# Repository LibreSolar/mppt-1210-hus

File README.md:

# 10A MPPT Charge Controller with USB

 Evaluation phase

User manual: [HTML](https://libre.solar/mppt-1210-hus/) / [PDF](https://libre.solar/mppt-1210-hus/manual.pdf)

Schematic: [PDF file](build/mppt-1210-hus_schematic.pdf)

Bill of Materials: [CSV file](build/mppt-1210-hus_bom.csv) or [interactive HTML BOM](https://libre.solar/mppt-1210-hus/mppt-1210-hus_ibom.html)

Firmware repository: [LibreSolar/charge-controller-firmware](https://github.com/LibreSolar/charge-controller-firmware)

## Features:

- 12V battery voltage
- 40V max. solar input (36 to 48-cell panels, ideally so-called 12V panels with 36 cells)
- 10A max. charge current
- 10A max. load output current
- Low-power 32bit ARM MCU (STM32L072)
- Expandable via Olimex Universal Extension Connector (UEXT) featuring
   I2C, Serial and SPI interface (e.g. used for display, WIFI communication, etc.)
- USB charging
- High-side load switching

## Built-in protection:

- Overvoltage
- Undervoltage
- Overcurrent
- PV short circuit
- PV reverse polarity
- Battery reverse polarity (destructive, fuse is blown)

## Manual

The manual is auto-generated from the markdown files in the `manual` subfolder. See [here](https://github.com/LibreSolar/md-manual-template) for further information regarding the automated deployment.

You can contribute to the manual by cloning the repository to your private GitHub workspace and sending pull-requests with upates you made.

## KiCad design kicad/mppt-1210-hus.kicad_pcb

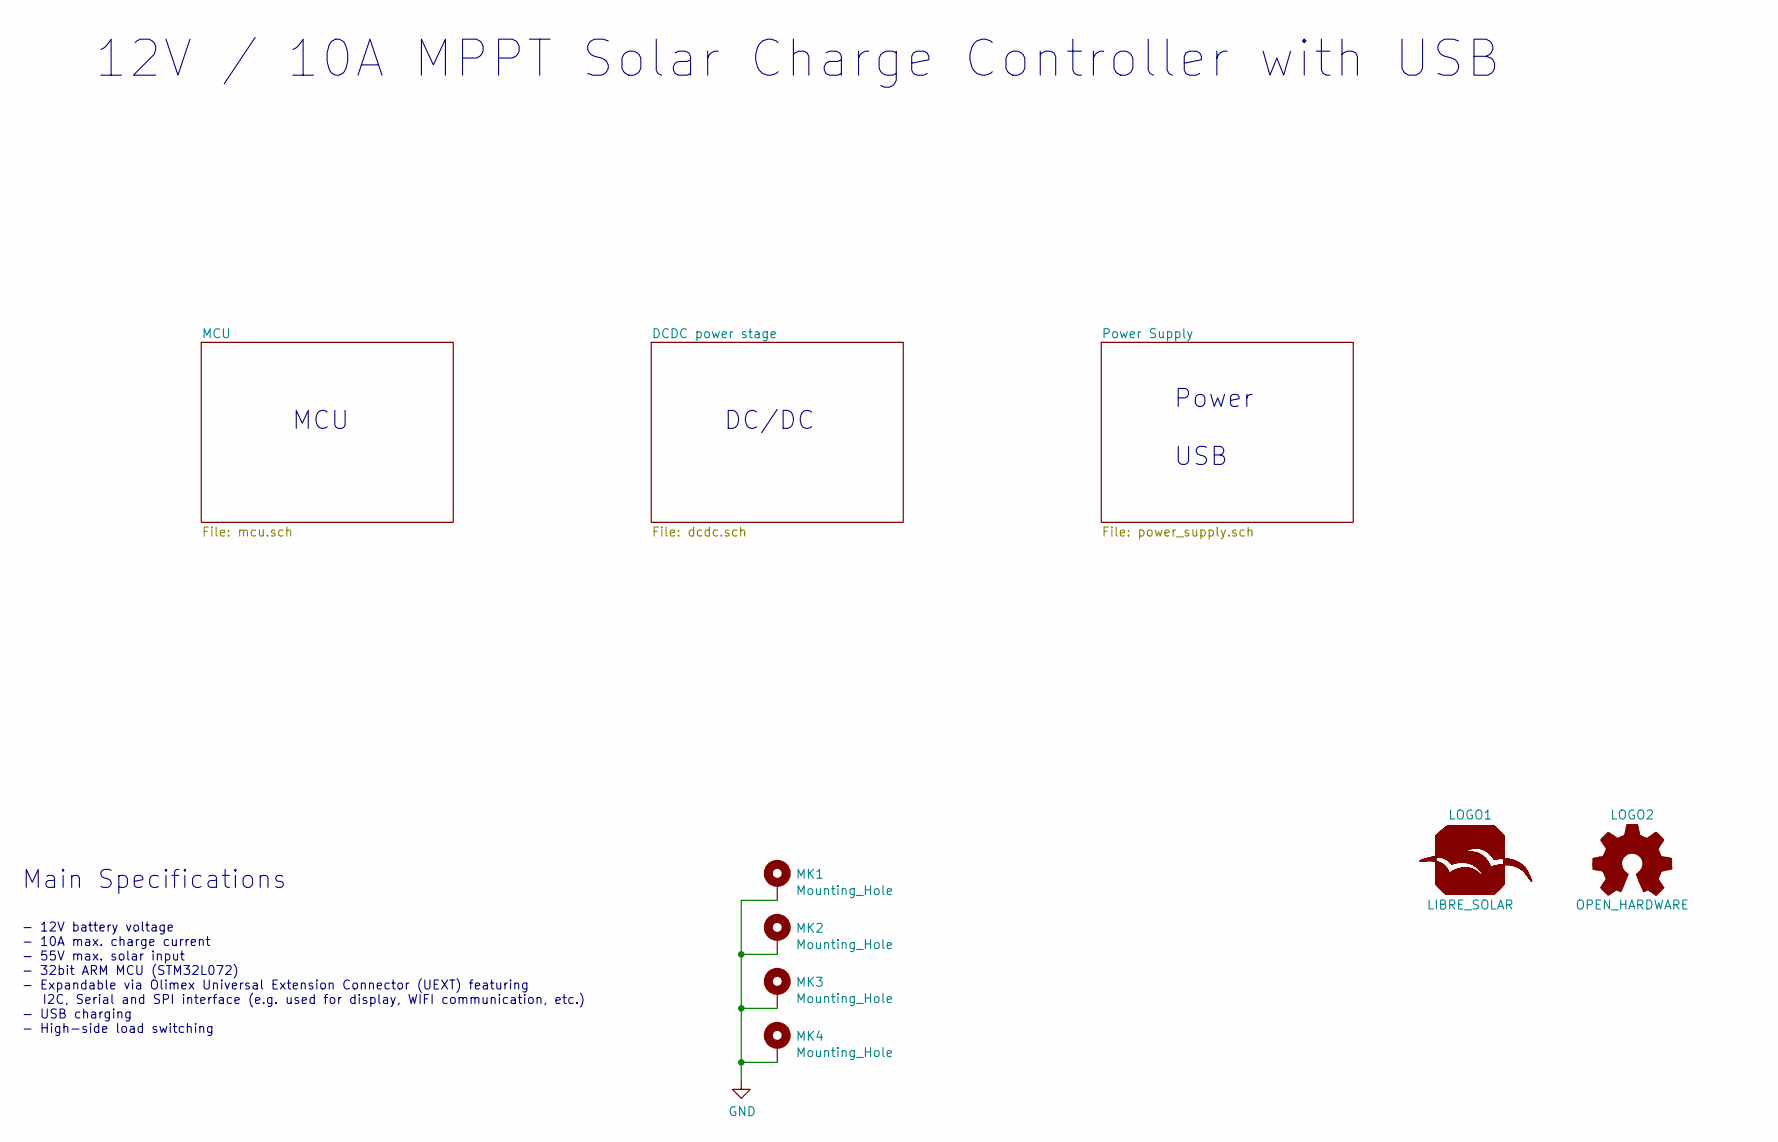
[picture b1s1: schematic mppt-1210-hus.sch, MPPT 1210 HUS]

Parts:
LOGO1: LIBRE_SOLAR; LIBRESOLAR_LOGO
LOGO2: OPEN_HARDWARE; OSHW-Logo_5.7x6mm_SilkScreen
MK1, MK2, MK3, MK4: Mounting_Hole; MountingHole_3.2mm_M3_Pad

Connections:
GND: MK1.1, MK2.1, MK3.1, MK4.1; also elsewhere on the board

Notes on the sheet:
12V / 10A MPPT Solar Charge Controller with USB
Main Specifications
- 12V battery voltage - 10A max. charge current - 55V max. solar input - 32bit ARM MCU (STM32L072) - Expandable via Olimex Universal Extension Connector (UEXT) featuring I2C, Serial and SPI interface (e.g. used for display, WIFI communication, etc.) - USB charging - High-side load switching
DC/DC
MCU
Power USB

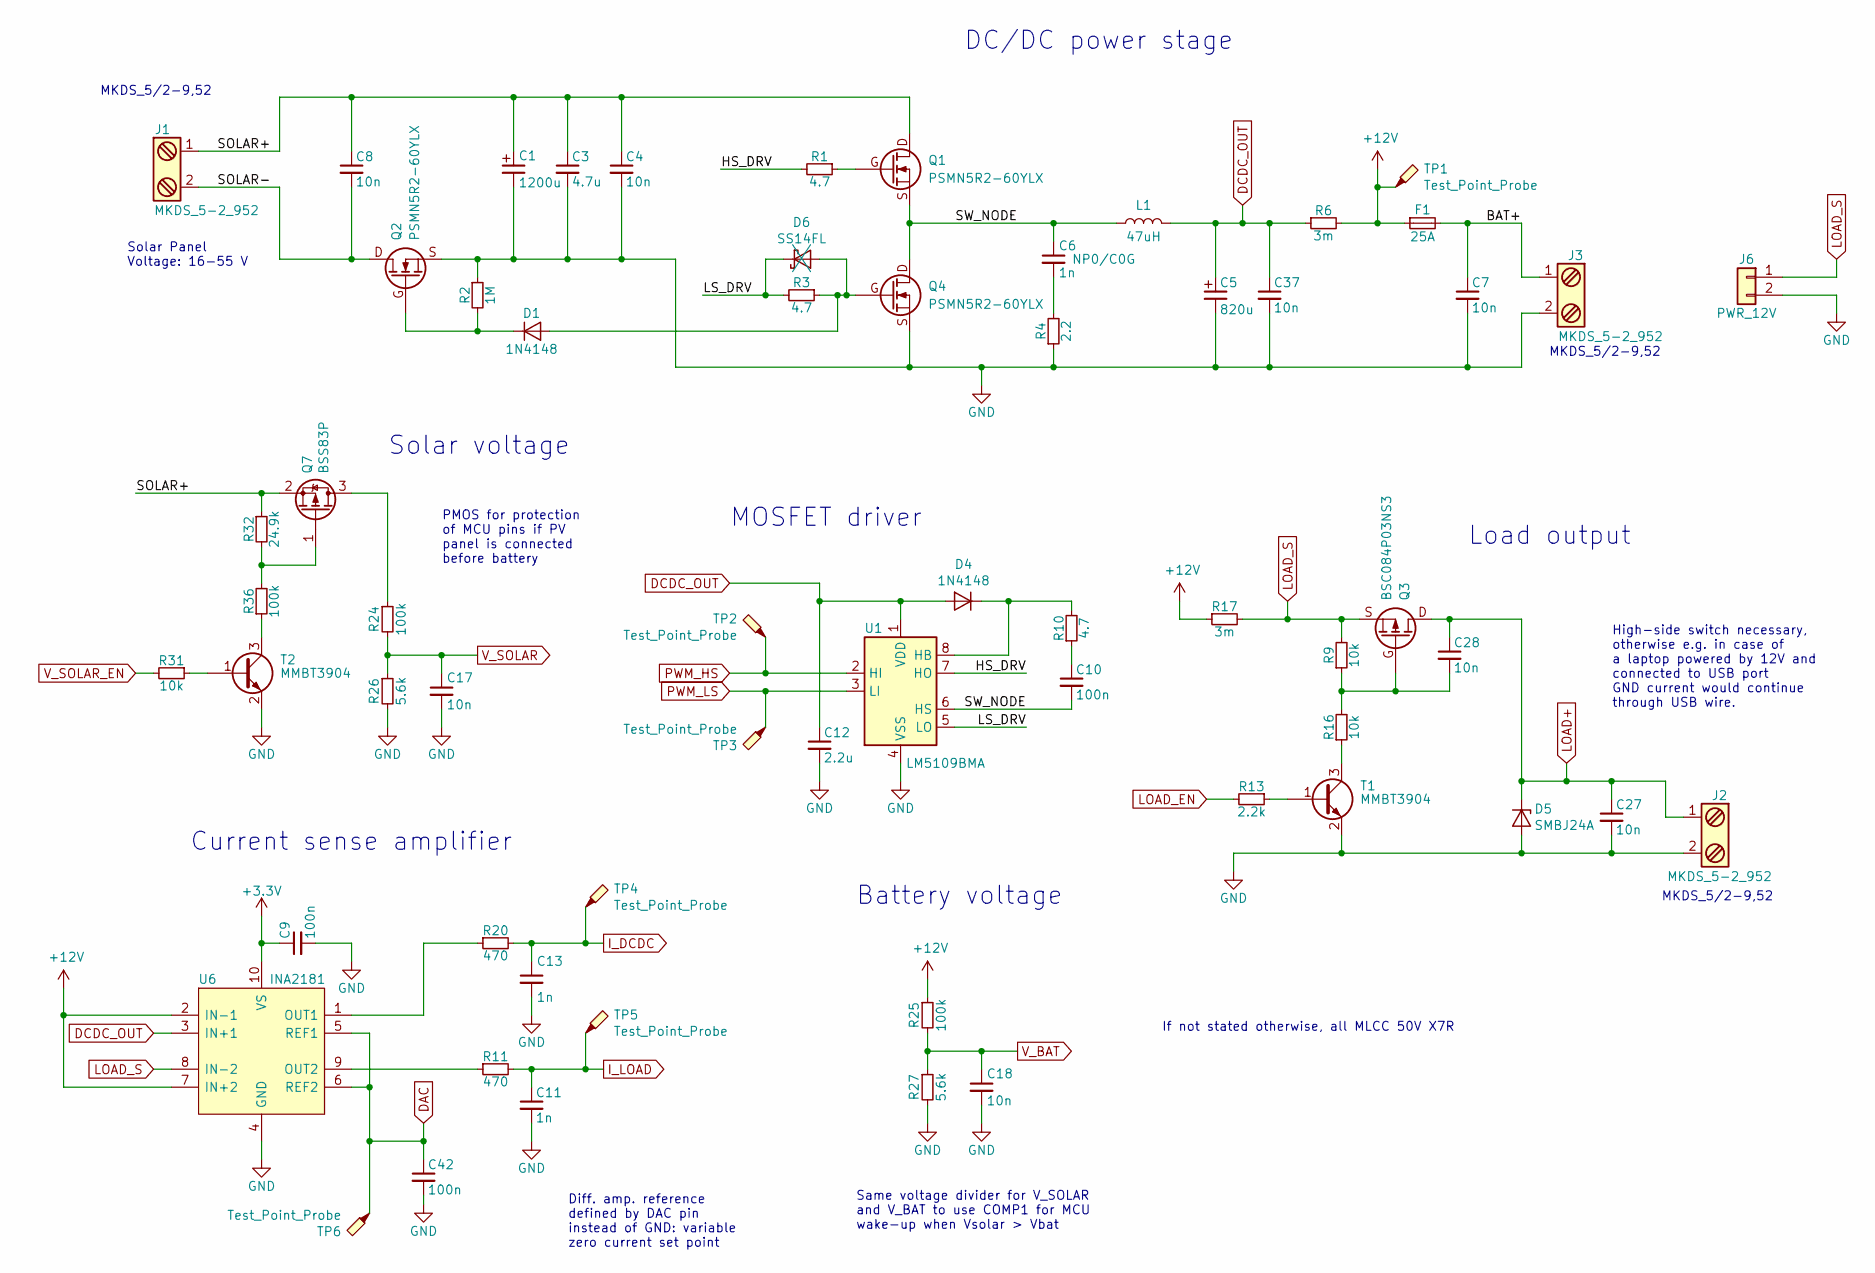
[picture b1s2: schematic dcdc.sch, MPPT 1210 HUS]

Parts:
C1: 1200u; CP_Radial_L31.5mm_D16.0mm_P7.50mm_horizontal; PartNumber EKYB630ELL122MLN3S
C3: 4.7u; C_1210_3225; PartNumber GRJ32DC72A475KE11L
C4, C7, C8, C17, C18, C27, C28, C37: 10n; C_0603_1608; PartNumber GCM188R72A103KA37D
C5: 820u; CP_Radial_D10.0mm_P5.00mm; PartNumber EEU-FR1E821
C6, C11, C13: 1n; C_0603_1608; PartNumber GRM1885C2A102JA01D
C9, C10, C42: 100n; C_0603_1608; PartNumber CC0603KRX7R9BB104
C12: 2.2u; C_0603_1608; PartNumber GRM188R61E225KA12D
D1, D4: 1N4148; D_SOD-123; PartNumber 1N4148W-7-F
D5: SMBJ24A; D_SMB; PartNumber SMBJ24A
D6: SS14FL; D_SOD-123; PartNumber SS14FL
F1: 25A; KEYSTONE-FUSE-3557-2; PartNumber 3557-2
J1, J2, J3: MKDS_5-2_952; Phoenix_Contact_MKDS_5-2-952; PartNumber 1714971
J6: PWR_12V; JST_XH_B02B-XH-A_1x02_P2.50mm_Vertical; PartNumber B2B-XH-A (LF)(SN)
L1: 47uH; L-FERYSTER-DTMSS-27_47uH; PartNumber DTMSS-27/0,047/15-HX
Q1, Q2, Q4: PSMN5R2-60YLX; 5X6_MOSFET; PartNumber PSMN5R2-60YLX
Q3: BSC084P03NS3; 5X6_MOSFET; PartNumber BSC084P03NS3GATMA1
Q7: BSS83P; SOT-23; PartNumber BSS83P H6327
R1, R3, R10: 4.7; R_0805_2012; PartNumber RC0805FR-074R7L
R2: 1M; R_0603_1608; PartNumber RC0603FR-071ML
R4: 2.2; R_1206_3216; PartNumber RC1206FR-072R2L
R6, R17: 3m; R_Bourns_CRE2512; PartNumber CRE2512-FZ-R003E-3
R9, R16, R31: 10k; R_0603_1608; PartNumber RC0603FR-0710KL
R11, R20: 470; R_0603_1608; PartNumber RC0603FR-07470RL
R13: 2.2k; R_0603_1608; PartNumber RC0603FR-072K2L
R24, R25, R36: 100k; R_0603_1608; PartNumber RC0603FR-07100KL
R26, R27: 5.6k; R_0603_1608; PartNumber RC0603FR-075K6L
R32: 24.9k; R_0603_1608; PartNumber RC0603FR-0724K9L
T1, T2: MMBT3904; SOT-23; PartNumber MMBT3904-7-F
TP1, TP2, TP3, TP4, TP5, TP6: Test_Point_Probe; TestPoint_Pad_D1.0mm
U1: LM5109BMA; SOIC-8_3.9x4.9mm_Pitch1.27mm; PartNumber LM5109BMAX/NOPB
U6: INA2181; VSSOP-10_3.0x3.0mm_P0.5mm; PartNumber INA2181A2IDGS

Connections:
+3V3: C9.1, U6.10 (VS); also elsewhere on the board
+12V: F1.1, R6.2, R17.1, R25.1, TP1.1, U6.2 (IN-1), U6.7 (IN+2)
/DCDC power stage/BAT+: C7.1, F1.2, J3.1
/DCDC power stage/HS_DRV: R1.2, U1.7 (HO)
/DCDC power stage/LS_DRV: D6.1 (K), R3.2, U1.5 (LO)
/DCDC power stage/SOLAR+: C1.1, C3.1, C4.1, C8.1, J1.1, Q1.D, Q7.2 (S), R32.1
/DCDC power stage/SOLAR-: C8.2, J1.2, Q2.D
/DCDC power stage/SW_NODE: C6.1, C10.2, L1.1, Q1.S, Q4.D, U1.6 (HS)
DAC: C42.1, TP6.1, U6.5 (REF1), U6.6 (REF2); also elsewhere on the board
DCDC_OUT: C5.1, C12.1, C37.1, D4.2 (A), L1.2, R6.1, U1.1 (VDD), U6.3 (IN+1); also elsewhere on the board
GND: C1.2, C3.2, C4.2, C5.2, C7.2, C9.2, C11.2, C12.2, C13.2, C17.2, C18.2, C27.2, C37.2, C42.2, D5.2 (A), J2.2, J3.2, J6.2, Q2.S, Q4.S, R2.1, R4.1, R26.2, R27.2, T1.2 (E), T2.2 (E), U1.4 (VSS), U6.4 (GND); also elsewhere on the board
I_DCDC: C13.1, R20.2, TP4.1; also elsewhere on the board
I_LOAD: C11.1, R11.2, TP5.1; also elsewhere on the board
LOAD+: C27.1, C28.1, D5.1 (K), J2.1, Q3.D
LOAD_EN: R13.2; also elsewhere on the board
LOAD_S: J6.1, Q3.S, R9.2, R17.2, U6.8 (IN-2); also elsewhere on the board
unnamed: C6.2, R4.2
unnamed: C10.1, R10.1
unnamed: C28.2, Q3.G, R9.1, R16.2
unnamed: D1.1 (K), Q2.G, R2.2
unnamed: D1.2 (A), D6.2 (A), Q4.G, R3.1
unnamed: D4.1 (K), R10.2, U1.8 (HB)
unnamed: Q1.G, R1.1
unnamed: Q7.1 (G), R32.2, R36.2
unnamed: Q7.3 (D), R24.1
unnamed: R11.1, U6.9 (OUT2)
unnamed: R13.1, T1.1 (B)
unnamed: R16.1, T1.3 (C)
unnamed: R20.1, U6.1 (OUT1)
unnamed: R31.1, T2.1 (B)
unnamed: R36.1, T2.3 (C)
PWM_HS: TP2.1, U1.2 (HI); also elsewhere on the board
PWM_LS: TP3.1, U1.3 (LI); also elsewhere on the board
V_BAT: C18.1, R25.2, R27.1; also elsewhere on the board
V_SOLAR: C17.1, R24.2, R26.1; also elsewhere on the board
V_SOLAR_EN: R31.2; also elsewhere on the board

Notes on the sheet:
Solar Panel Voltage: 16-55 V
DC/DC power stage
Load output
MOSFET driver
If not stated otherwise, all MLCC 50V X7R
MKDS_5/2-9,52
Current sense amplifier
Solar voltage
Diff. amp. reference defined by DAC pin instead of GND: variable zero current set point
Same voltage divider for V_SOLAR and V_BAT to use COMP1 for MCU wake-up when Vsolar > Vbat
High-side switch necessary, otherwise e.g. in case of a laptop powered by 12V and connected to USB port GND current would continue through USB wire.
Battery voltage
PMOS for protection of MCU pins if PV panel is connected before battery

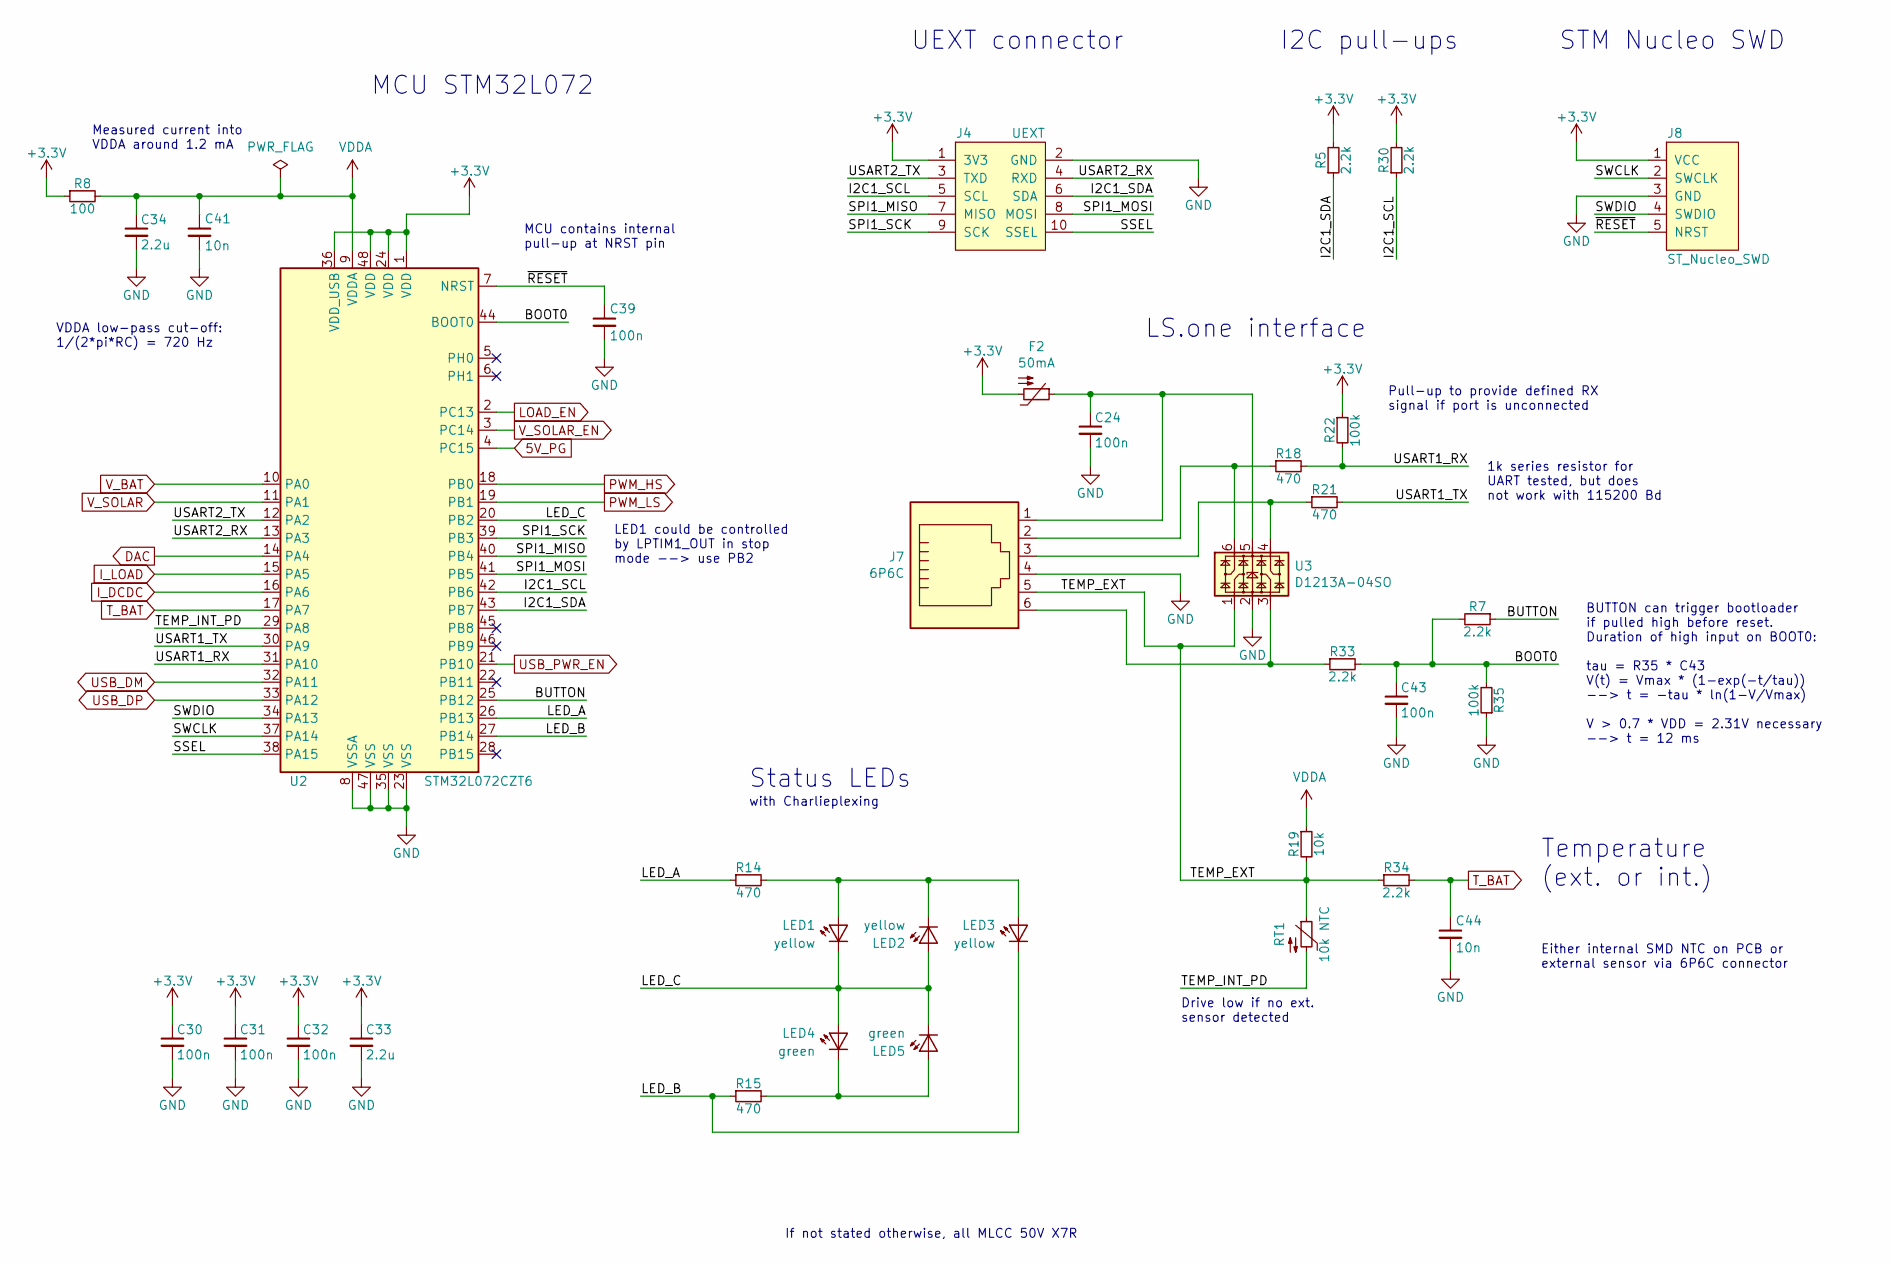
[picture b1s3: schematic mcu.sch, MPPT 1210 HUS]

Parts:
C24, C30, C31, C32, C39, C43: 100n; C_0603_1608; PartNumber CC0603KRX7R9BB104
C33, C34: 2.2u; C_0603_1608; PartNumber GRM188R61E225KA12D
C41, C44: 10n; C_0603_1608; PartNumber GCM188R72A103KA37D
F2: 50mA; R_1206_3216; PartNumber 0ZCJ0005FF2E
J4: UEXT; Box_Header_2x05x2.54mm_Straight; PartNumber 302-S101
J7: 6P6C; RJ25_6P6C_TabUp; PartNumber 615006138421
J8: ST_Nucleo_SWD; PinHeader_1x05_P2.54mm_Vertical; PartNumber M20-9990546
LED1, LED3: yellow; LED_0603_D3.0mm; PartNumber LTST-C191KSKT
LED2, LED5: green; LED_0603_D3.0mm; PartNumber LTST-C190KGKT
R5, R7, R30, R33, R34: 2.2k; R_0603_1608; PartNumber RC0603FR-072K2L
R8: 100; R_0603_1608; PartNumber RC0603FR-07100RL
R14, R15, R18, R21: 470; R_0603_1608; PartNumber RC0603FR-07470RL
R19: 10k; R_0603_1608; PartNumber RC0603FR-0710KL
R22, R35: 100k; R_0603_1608; PartNumber RC0603FR-07100KL
RT1: 10k NTC; R_0603_1608; PartNumber NCU18XH103E6SRB
U2: STM32L072CZT6; LQFP-48_7x7mm_P0.5mm; PartNumber STM32L072CZT6
U3: D1213A-04SO; SOT-23-6; PartNumber D1213A-04SO

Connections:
5V_PG: U2.4 (PC15); also elsewhere on the board
+3V3: C30.1, C31.1, C32.1, C33.1, F2.2, J4.1 (3V3), J8.1 (VCC), R5.2, R8.1, R22.1, R30.2, U2.1 (VDD), U2.24 (VDD), U2.36 (VDD_USB), U2.48 (VDD); also elsewhere on the board
/MCU/BOOT0: C43.1, R7.2, R33.2, R35.2, U2.44 (BOOT0)
/MCU/BUTTON: R7.1, U2.25 (PB12)
/MCU/I2C1_SCL: J4.5 (SCL), R30.1, U2.42 (PB6)
/MCU/I2C1_SDA: J4.6 (SDA), R5.1, U2.43 (PB7)
/MCU/LED_A: R14.1, U2.26 (PB13)
/MCU/LED_B: LED3.1 (K), R15.1, U2.27 (PB14)
/MCU/LED_C: LED1.1 (K), LED2.2 (A), LED5.1 (K), U2.20 (PB2); also elsewhere on the board
/MCU/SPI1_MISO: J4.7 (MISO), U2.40 (PB4)
/MCU/SPI1_MOSI: J4.8 (MOSI), U2.41 (PB5)
/MCU/SPI1_SCK: J4.9 (SCK), U2.39 (PB3)
/MCU/SSEL: J4.10 (SSEL), U2.38 (PA15)
/MCU/SWCLK: J8.2 (SWCLK), U2.37 (PA14)
/MCU/SWDIO: J8.4 (SWDIO), U2.34 (PA13)
/MCU/TEMP_EXT: J7.5, R19.2, R34.1, RT1.1, U3.1
/MCU/TEMP_INT_PD: RT1.2, U2.29 (PA8)
/MCU/USART1_RX: R18.2, R22.2, U2.31 (PA10)
/MCU/USART1_TX: R21.2, U2.30 (PA9)
/MCU/USART2_RX: J4.4 (RXD), U2.13 (PA3)
/MCU/USART2_TX: J4.3 (TXD), U2.12 (PA2)
/MCU/~RESET: C39.1, J8.5 (NRST), U2.7 (NRST)
DAC: U2.14 (PA4); also elsewhere on the board
GND: C24.2, C30.2, C31.2, C32.2, C33.2, C34.2, C39.2, C41.2, C43.2, C44.2, J4.2 (GND), J7.4, J8.3 (GND), R35.1, U2.8 (VSSA), U2.23 (VSS), U2.35 (VSS), U2.47 (VSS), U3.2; also elsewhere on the board
I_DCDC: U2.16 (PA6); also elsewhere on the board
I_LOAD: U2.15 (PA5); also elsewhere on the board
LOAD_EN: U2.2 (PC13); also elsewhere on the board
unnamed: C24.1, F2.1, J7.1, U3.5
unnamed: J7.2, R18.1, U3.6
unnamed: J7.3, R21.1, U3.4
unnamed: J7.6, R33.1, U3.3
PWM_HS: U2.18 (PB0); also elsewhere on the board
PWM_LS: U2.19 (PB1); also elsewhere on the board
T_BAT: C44.1, R34.2, U2.17 (PA7)
USB_DM: U2.32 (PA11); also elsewhere on the board
USB_DP: U2.33 (PA12); also elsewhere on the board
USB_PWR_EN: U2.21 (PB10); also elsewhere on the board
VDDA: C34.1, C41.1, R8.2, R19.1, U2.9 (VDDA)
V_BAT: U2.10 (PA0); also elsewhere on the board
V_SOLAR: U2.11 (PA1); also elsewhere on the board
V_SOLAR_EN: U2.3 (PC14); also elsewhere on the board

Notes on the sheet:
Status LEDs
MCU STM32L072
STM Nucleo SWD
If not stated otherwise, all MLCC 50V X7R
UEXT connector
I2C pull-ups
MCU contains internal pull-up at NRST pin
LED1 could be controlled by LPTIM1_OUT in stop mode --> use PB2
Measured current into VDDA around 1.2 mA
VDDA low-pass cut-off: 1/(2*pi*RC) = 720 Hz
with Charlieplexing
Temperature (ext. or int.)
Either internal SMD NTC on PCB or external sensor via 6P6C connector
LS.one interface
Drive low if no ext. sensor detected
1k series resistor for UART tested, but does not work with 115200 Bd
BUTTON can trigger bootloader if pulled high before reset. Duration of high input on BOOT0: tau = R35 * C43 V(t) = Vmax * (1-exp(-t/tau)) --> t = -tau * ln(1-V/Vmax) V > 0.7 * VDD = 2.31V necessary --> t = 12 ms
Pull-up to provide defined RX signal if port is unconnected

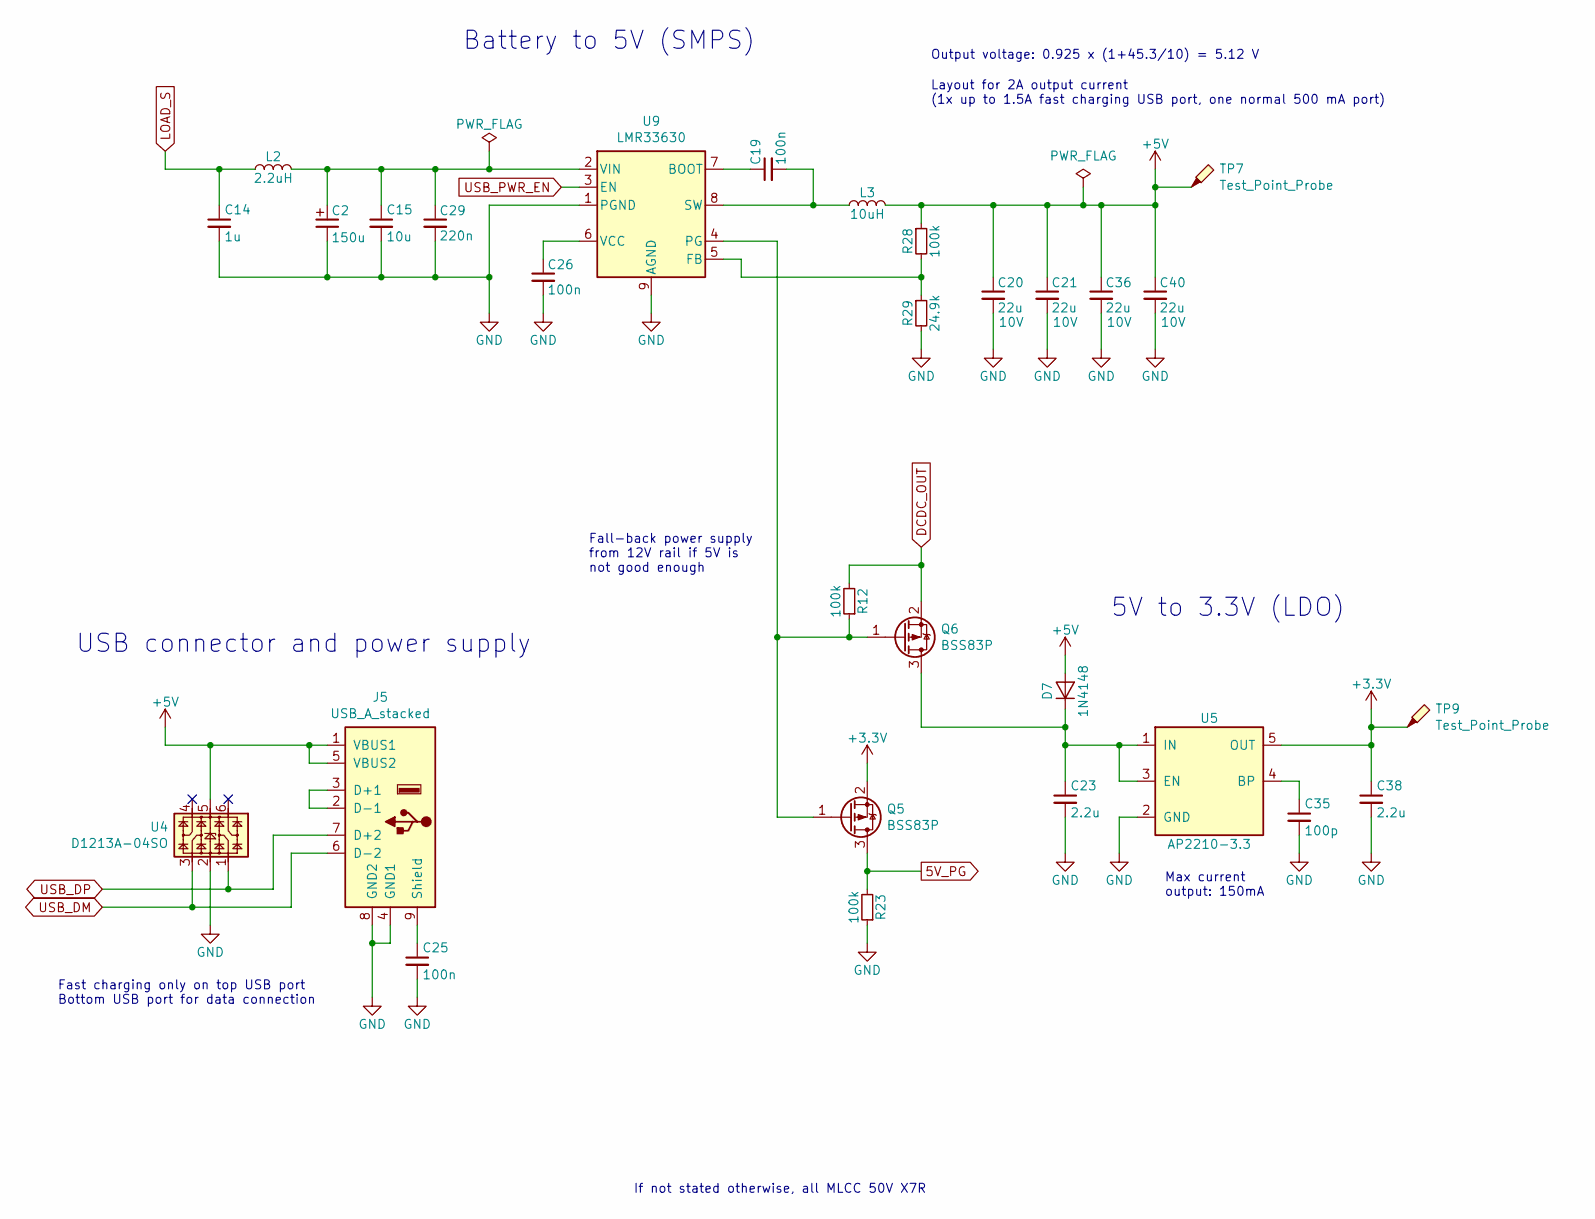
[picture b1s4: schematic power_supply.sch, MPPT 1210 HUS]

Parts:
C2: 150u; CP_Elec_8x6.2; PartNumber EEEFK1E151P
C14: 1u; C_0805_2012; PartNumber CC0805KKX7R9BB105
C15: 10u; C_1210_3225; PartNumber CL31A106KAHNNNE
C19, C25, C26: 100n; C_0603_1608; PartNumber CC0603KRX7R9BB104
C20, C21, C36, C40: 22u; C_1206_3216; PartNumber CL31B226MPHNNNE
C23, C38: 2.2u; C_0603_1608; PartNumber GRM188R61E225KA12D
C29: 220n; C_0603_1608; PartNumber GCM188R71E224KA55D
C35: 100p; C_0603_1608; PartNumber CC0603JRNPO9BN101
D7: 1N4148; D_SOD-123; PartNumber 1N4148W-7-F
J5: USB_A_stacked; USB_A_Wuerth_61400826021_Horizontal_Stacked; PartNumber UJ2-ADH-1-TH
L2: 2.2uH; L_1210_3225Metric; PartNumber BRL3225T2R2M
L3: 10uH; Bourns_SRN8040TA; PartNumber NR8040T100M
Q5, Q6: BSS83P; SOT-23; PartNumber BSS83P H6327
R12, R23, R28: 100k; R_0603_1608; PartNumber RC0603FR-07100KL
R29: 24.9k; R_0603_1608; PartNumber RC0603FR-0724K9L
TP7, TP9: Test_Point_Probe; TestPoint_Pad_D1.0mm
U4: D1213A-04SO; SOT-23-6; PartNumber D1213A-04SO
U5: AP2210-3.3; SOT-23-5; PartNumber AP2210K-3.3TRG1
U9: LMR33630; TI_SO-PowerPAD-8_ThermalVias; PartNumber LMR33630ADDA

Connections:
5V_PG: Q5.3 (D), R23.2; also elsewhere on the board
+3V3: C38.1, Q5.2 (S), TP9.1, U5.5 (OUT); also elsewhere on the board
+5V: C20.1, C21.1, C36.1, C40.1, D7.2 (A), J5.1 (VBUS1), J5.5 (VBUS2), L3.2, R28.1, TP7.1, U4.5
DCDC_OUT: Q6.2 (S), R12.2; also elsewhere on the board
GND: C2.2, C14.2, C15.2, C20.2, C21.2, C23.2, C25.2, C26.2, C29.2, C35.2, C36.2, C38.2, C40.2, J5.4 (GND1), J5.8 (GND2), R23.1, R29.2, U4.2, U5.2 (GND), U9.1 (PGND), U9.9 (AGND); also elsewhere on the board
LOAD_S: C14.1, L2.1; also elsewhere on the board
unnamed: C2.1, C15.1, C29.1, L2.2, U9.2 (VIN)
unnamed: C19.1, U9.7 (BOOT)
unnamed: C19.2, L3.1, U9.8 (SW)
unnamed: C23.1, D7.1 (K), Q6.3 (D), U5.1 (IN), U5.3 (EN)
unnamed: C25.1, J5.9 (Shield)
unnamed: C26.1, U9.6 (VCC)
unnamed: C35.1, U5.4 (BP)
unnamed: J5.2 (D-1), J5.3 (D+1)
unnamed: Q5.1 (G), Q6.1 (G), R12.1, U9.4 (PG)
unnamed: R28.2, R29.1, U9.5 (FB)
USB_DM: J5.6 (D-2), U4.3; also elsewhere on the board
USB_DP: J5.7 (D+2), U4.1; also elsewhere on the board
USB_PWR_EN: U9.3 (EN); also elsewhere on the board

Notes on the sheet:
Battery to 5V (SMPS)
5V to 3.3V (LDO)
If not stated otherwise, all MLCC 50V X7R
Output voltage: 0.925 x (1+45.3/10) = 5.12 V
USB connector and power supply
Layout for 2A output current (1x up to 1.5A fast charging USB port, one normal 500 mA port)
Fast charging only on top USB port Bottom USB port for data connection
Fall-back power supply from 12V rail if 5V is not good enough
Max current output: 150mA

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
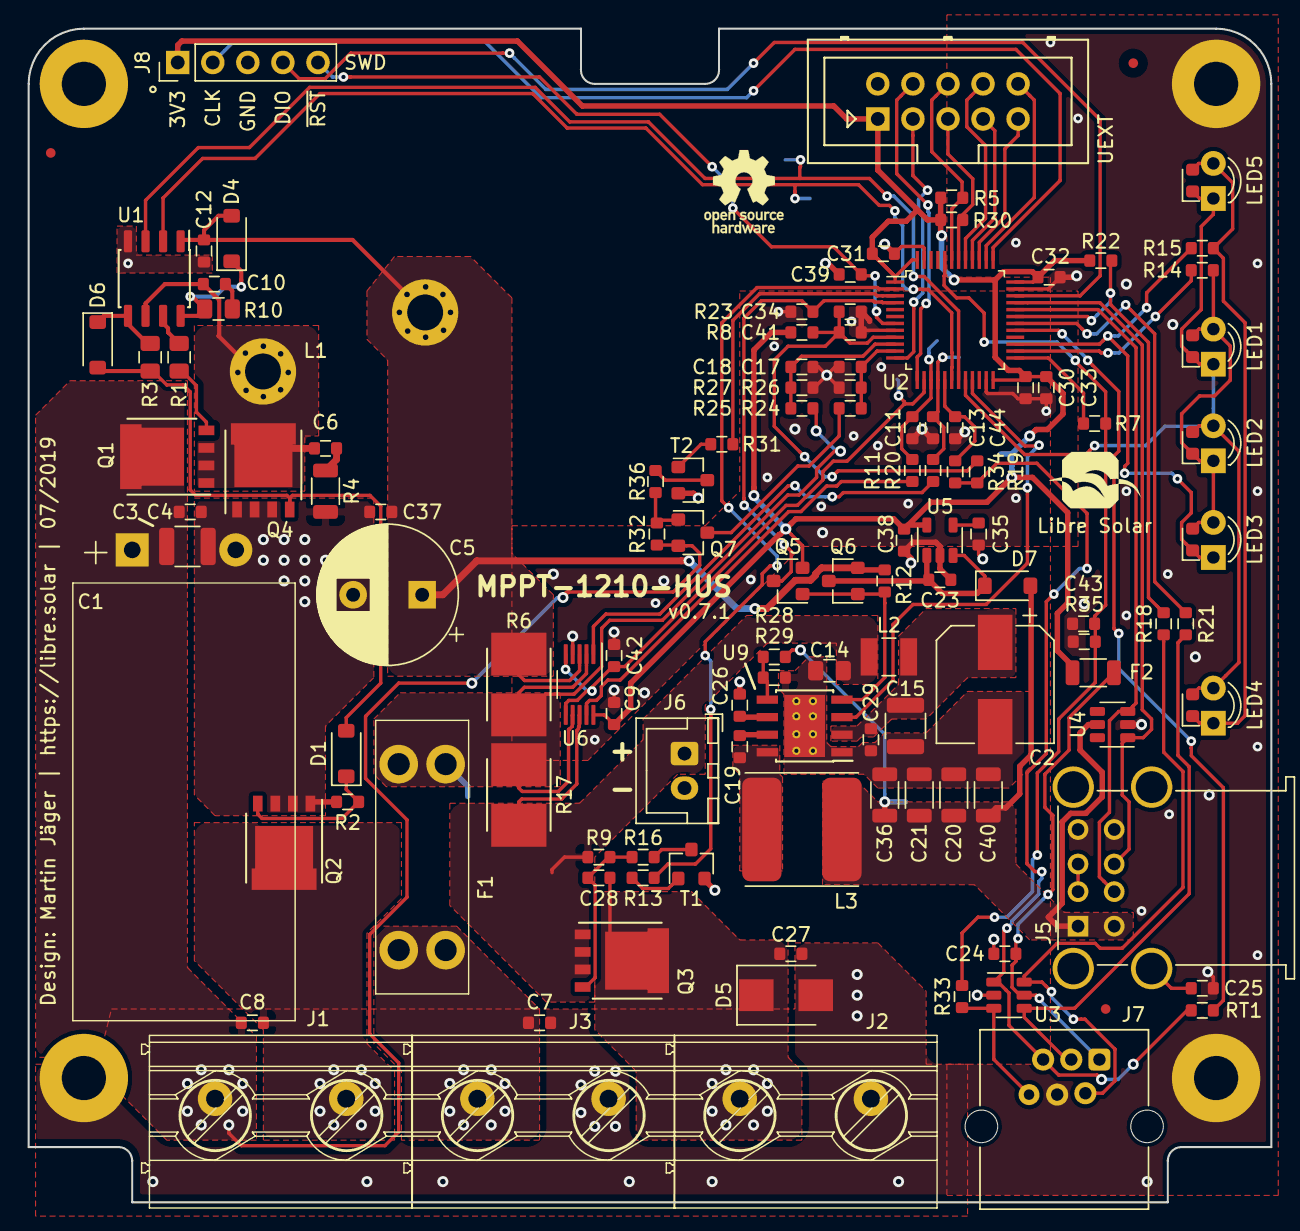
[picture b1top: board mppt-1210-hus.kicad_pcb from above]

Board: 2 copper layers, 90.0 x 85.0 mm, 132 parts (0 on the bottom side), 79 nets.

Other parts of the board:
LED4: green; LED_0603_D3.0mm

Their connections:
/MCU/LED_C: LED4.2; also elsewhere on the board

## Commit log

2019-01-09 Initial commit (PCB revision 0.2)
2019-01-09 PDF schematic added
2019-01-09 Several improvements (v0.4) after first tests
    - Ultra-low-power MCU STM32L072
    - Larger screw terminals
    - USB power supply replaced by more efficient SMPS
    - High-side load switch with P-MOS
    - High-side current measurement to include USB current in load measurement
2019-04-02 Board shape adjusted and 6P6C connector added
2019-04-16 Solar voltage input protection added
2019-06-29 Small changes and files renamed
2019-06-30 First draft of user manual added
2019-07-01 GitHub linguist settings adjusted to recognize as KiCad
2019-07-05 Updates in user manual
2019-07-25 Small adjustments after testing
    - MOSFET gate driver changed to reduce switch node ringing
    - Current measurement output filter time constant reduced to have less delay
    - BTN pin allows starting the bootloader if pulled to 3V3 before startup
2020-04-20 Update specs and reduce max. input voltage
2020-04-20 Add automatically deployed interactive BOM
2021-05-02 Update documentation and license
    - Change license to CERN-OHL-W-2.0, which is more suitable for hardware
    - Add build folder including CSV and interactive BOM
    - Don't auto-generate interactive BOM anymore
    - Update schematic template and text fields
    - Use photo instead of rendered image
    - Rename branch master to main
2021-05-02 Deploy LibreSolar/mppt-1210-hus to github.com/LibreSolar/mppt-1210-hus.git:gh-pages
2021-07-22 Add kitspace.yaml
2022-10-05 add LED indicator table
    add LED indicator table for quick overview of LED functions

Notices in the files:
kicad/dcdc.sch:
Copyright © 2019 Libre Solar Technologies GmbH
Licensed under CERN-OHL-W version 2
